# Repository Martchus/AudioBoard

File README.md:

# AudioBoard

Im Ordner Hardware befindet sich der Schaltplan als KiCAD Projekt und die Gerberdaten der Platine.

Die Software gibt es als "Basic" Version, welche die Grundlegenden Funktionen zur verfügung stellt. Auf der Basis von diesen Daten können eigene Projekte entwickelt werden.
Der Quelltext zum Matrixprojekt ist auf genau dieses Projekt zugeschnitten. Es wird dazu eine 7x6 Matrix mit WS2812 LEDs erwartete, welche alle seriell verbunden sind. Dieser Quelltext soll eher als Inspiration dienen.

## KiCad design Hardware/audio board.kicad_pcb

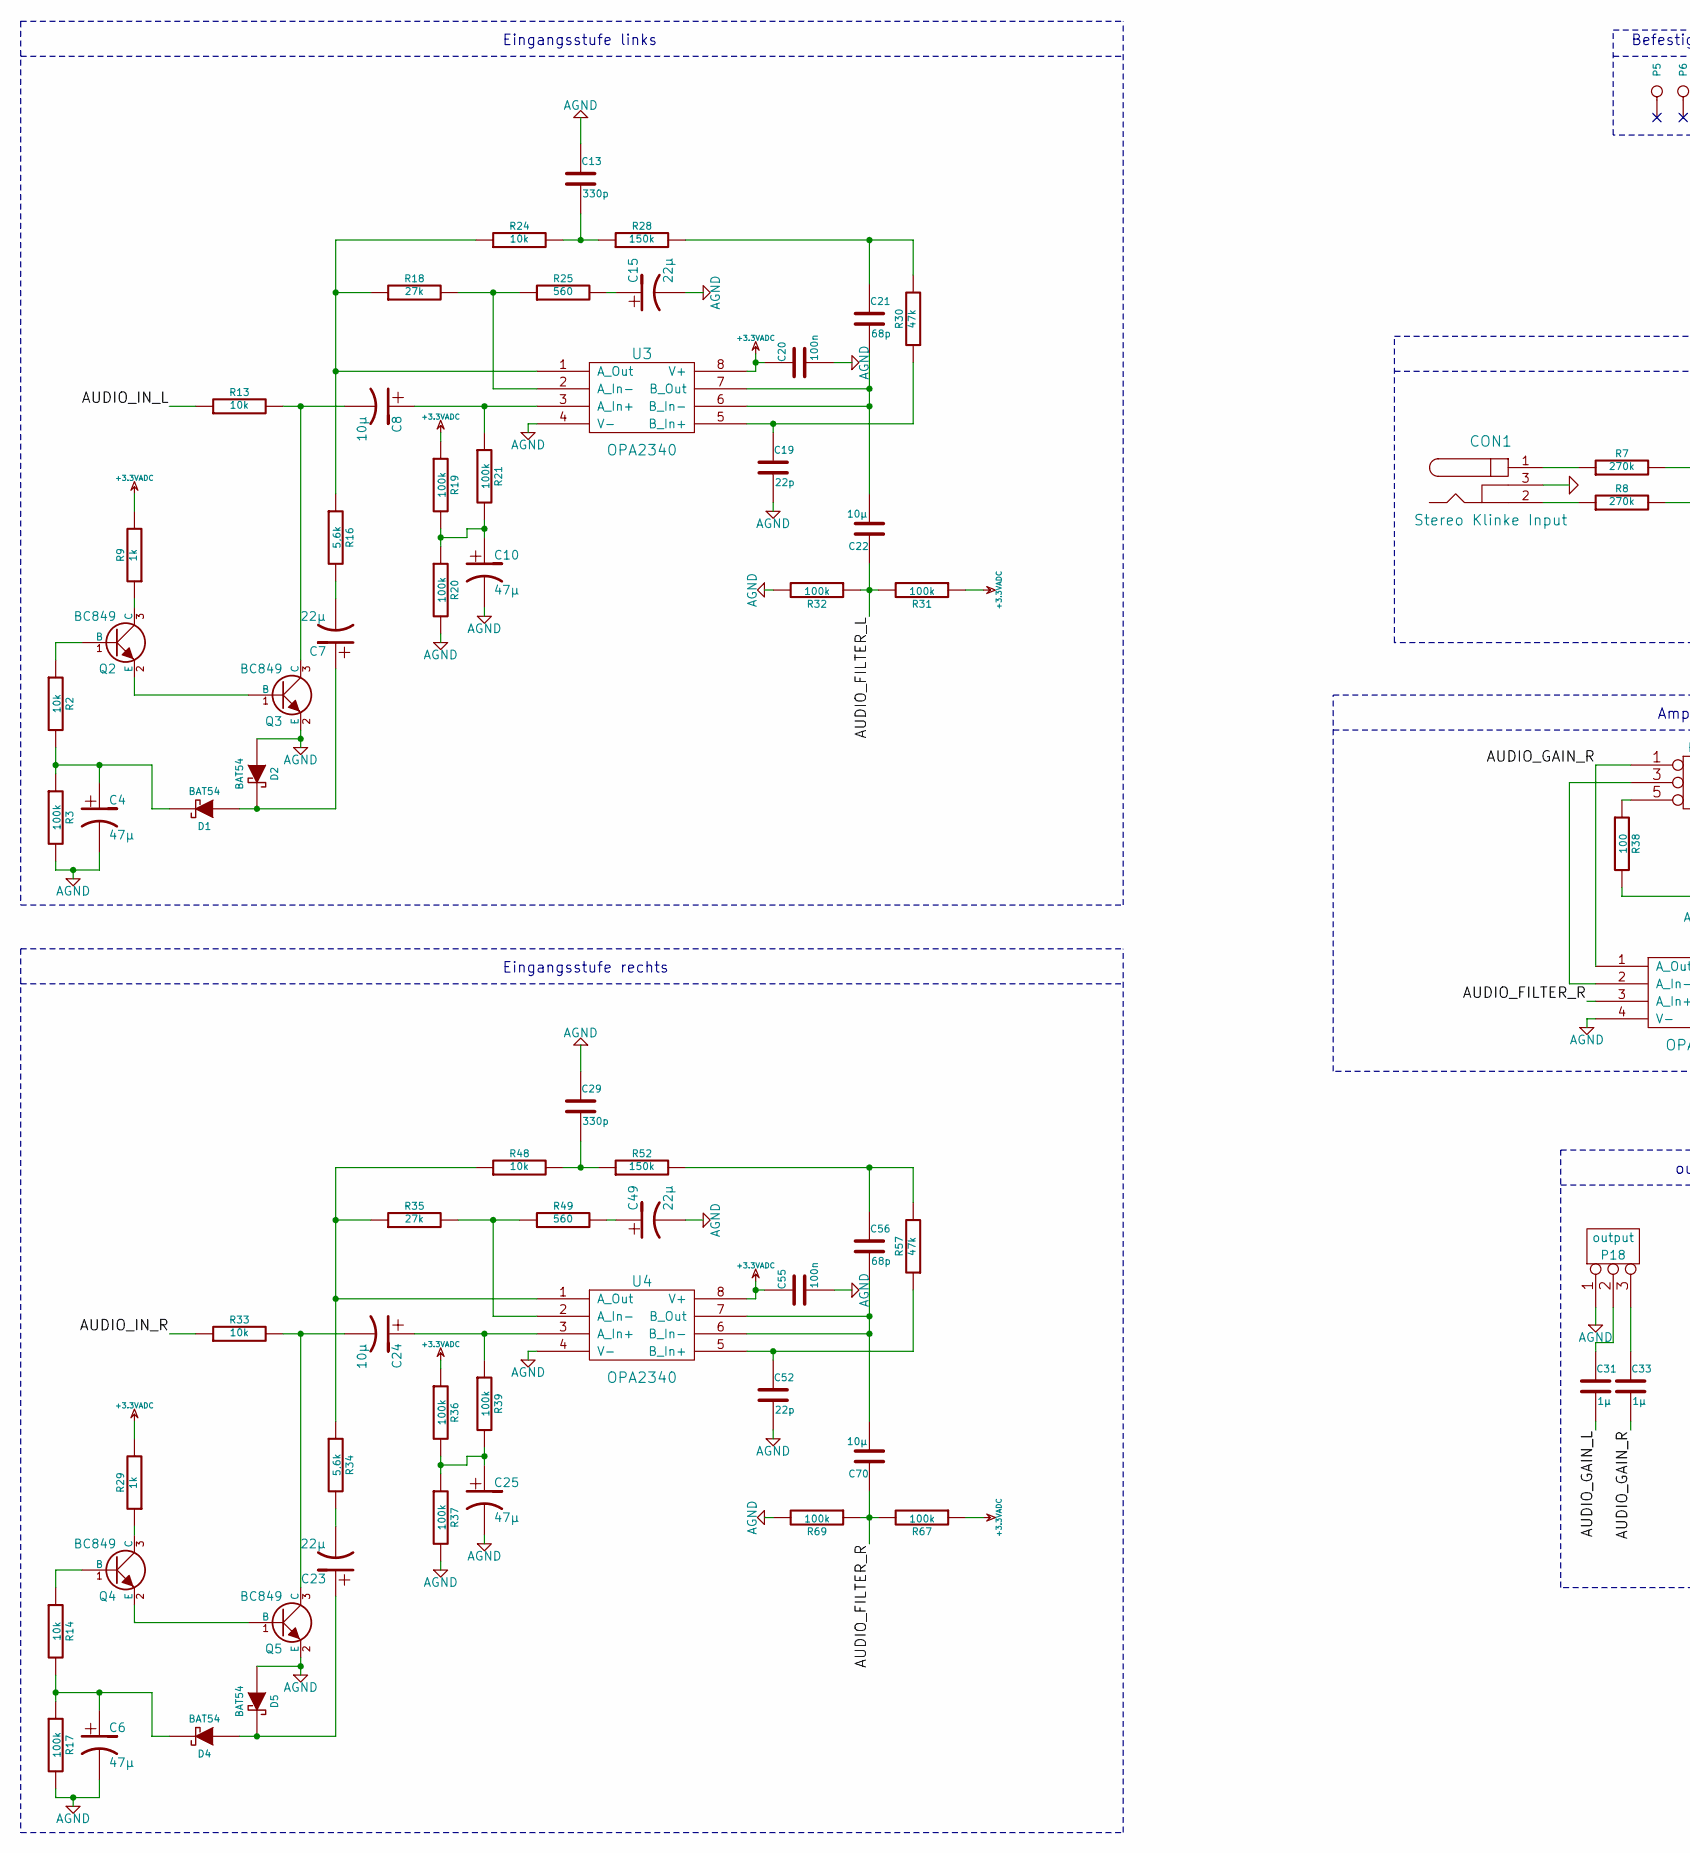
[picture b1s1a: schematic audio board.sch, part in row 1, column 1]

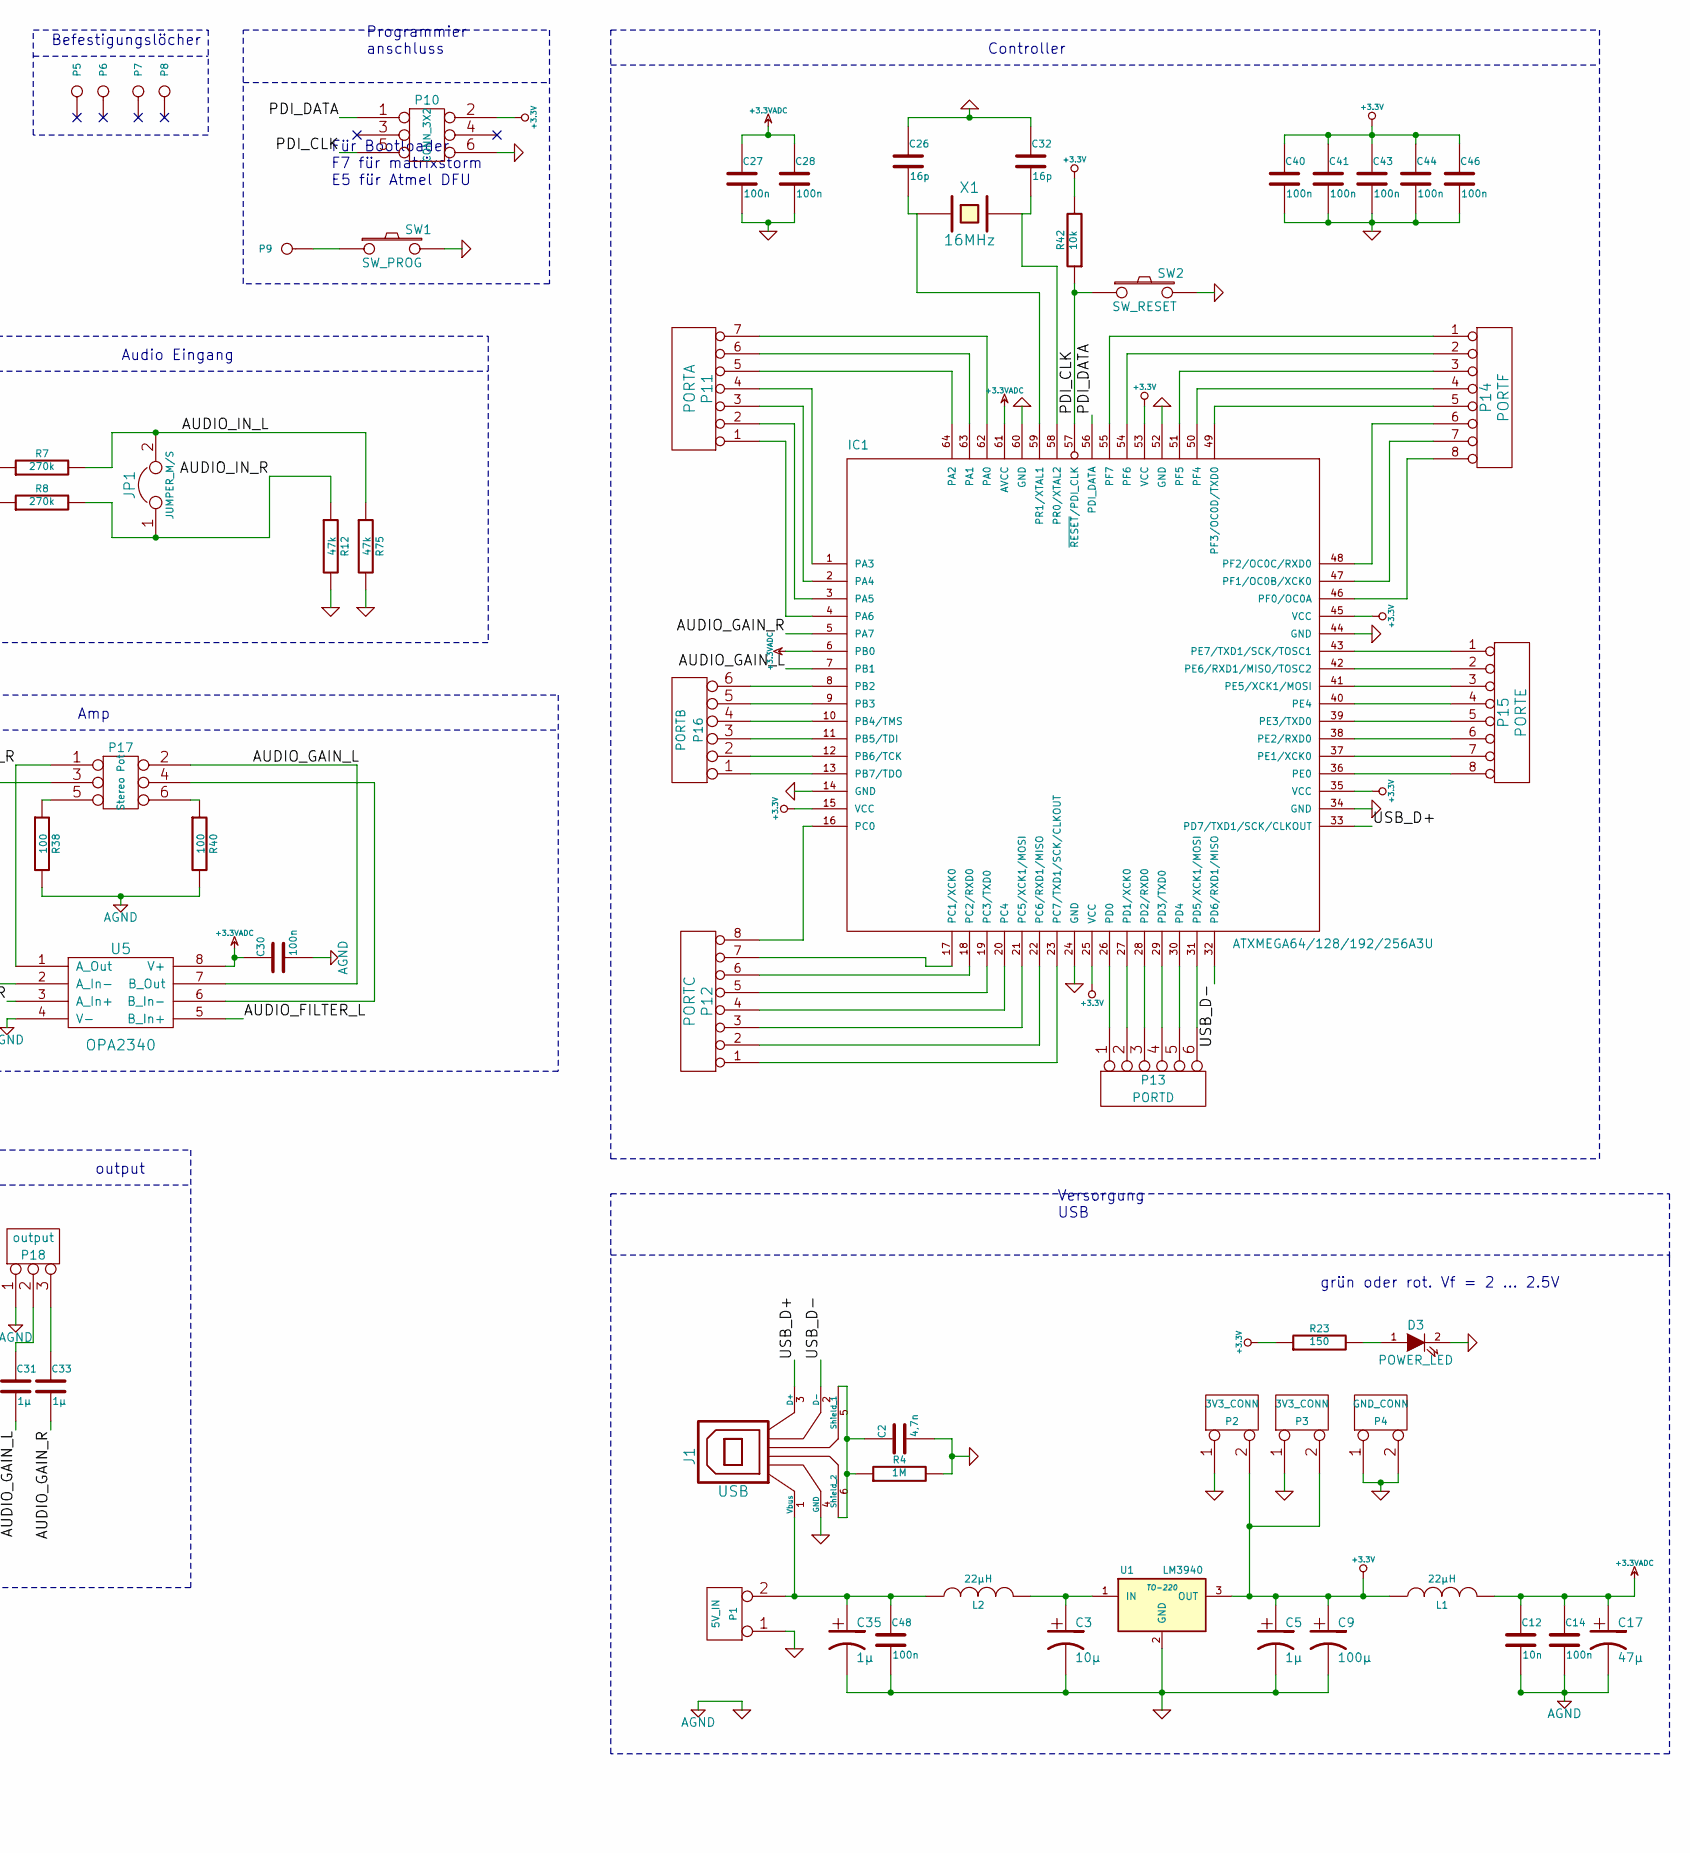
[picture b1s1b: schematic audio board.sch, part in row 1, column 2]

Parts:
C2: 4,7n
C3, C8, C22, C24, C70: 10µ
C4, C6, C10, C17, C25: 47µ
C5, C31, C33, C35: 1µ
C7, C15, C23, C49: 22µ
C9: 100µ
C12: 10n
C13, C29: 330p
C14, C20, C27, C28, C30, C40, C41, C43, C44, C46, C48, C55: 100n
C19, C52: 22p
C21, C56: 68p
C26, C32: 16p
CON1: Stereo Klinke Input
D1, D2, D4, D5: BAT54
D3: POWER_LED
IC1: ATXMEGA64/128/192/256A3U; TQFP64
J1: USB
JP1: JUMPER_M/S
L1, L2: 22µH
P1: 5V_IN
P2, P3: 3V3_CONN
P4: GND_CONN
P5, P6, P7, P8: Bohrung
P9: CONN_1
P10: CONN_3X2
P11: PORTA
P12: PORTC
P13: PORTD
P14: PORTF
P15: PORTE
P16: PORTB
P17: Stereo Pot
P18: output
Q2, Q3, Q4, Q5: BC849
R2, R13, R14, R24, R33, R42, R48: 10k
R3, R17, R19, R20, R21, R31, R32, R36, R37, R39, R67, R69: 100k
R4: 1M
R7, R8: 270k
R9, R29: 1k
R12, R30, R57, R75: 47k
R16, R34: 5,6k
R18, R35: 27k
R23: 150
R25, R49: 560
R28, R52: 150k
R38, R40: 100
SW1: SW_PROG
SW2: SW_RESET
U1: LM3940; TO-220
U3, U4, U5: OPA2340
X1: 16MHz

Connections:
+3.3V: C5.1, C9.1, C40.1, C41.1, C43.1, C44.1, C46.1, IC1.15 (VCC), IC1.25 (VCC), IC1.35 (VCC), IC1.45 (VCC), IC1.53 (VCC), L1.1, P2.2 (PM), P3.2 (PM), P10.2, R23.1, R42.2, U1.3 (OUT)
+3.3VADC: C12.1, C14.1, C17.1, C20.1, C27.1, C28.1, C30.1, C55.1, IC1.6 (PB0), IC1.61 (AVCC), L1.2, R9.2, R19.1, R29.2, R31.1, R36.1, R67.1, U3.8 (V+), U4.8 (V+), U5.8 (V+)
/AUDIO_FILTER_L: C22.1, R31.2, R32.1, U5.5 (B_In+)
/AUDIO_FILTER_R: C70.1, R67.2, R69.1, U5.3 (A_In+)
/AUDIO_GAIN_L: C31.2, IC1.7 (PB1), P17.2, U5.7 (B_Out)
/AUDIO_GAIN_R: C33.2, IC1.5 (PA7), P17.1, U5.1 (A_Out)
/AUDIO_IN_L: JP1.2, R7.2, R13.1, R75.1
/AUDIO_IN_R: JP1.1, R8.2, R12.1, R33.1
/PDI_CLK: IC1.57 (~RESET~/PDI_CLK), P10.5, R42.1, SW2.1
/PDI_DATA: IC1.56 (PDI_DATA), P10.1
/USB_D+: IC1.33 (PD7/TXD1/SCK/CLKOUT), J1.3 (D+)
/USB_D-: IC1.32 (PD6/RXD1/MISO), J1.2 (D-)
AGND: C2.2, C3.2, C4.2, C5.2, C6.2, C9.2, C10.2, C12.2, C13.1, C14.2, C15.2, C17.2, C19.2, C20.2, C25.2, C26.1, C27.2, C28.2, C29.1, C30.2, C32.1, C35.2, C40.2, C41.2, C43.2, C44.2, C46.2, C48.2, C49.2, C52.2, C55.2, CON1.3, D2.1 (A), D3.2 (K), D5.1 (A), IC1.14 (GND), IC1.24 (GND), IC1.34 (GND), IC1.44 (GND), IC1.52 (GND), IC1.60 (GND), J1.4 (GND), P1.1, P2.1, P3.1, P4.1, P4.2 (PM), P10.6, P18.1, Q3.2 (E), Q5.2 (E), R3.2, R4.2, R12.2, R17.2, R20.2, R32.2, R37.2, R38.2, R40.2, R69.2, R75.2, SW1.2, SW2.2, U1.2 (GND), U3.4 (V-), U4.4 (V-), U5.4 (V-)
unnamed: IC1.46 (PF0/OC0A), P14.8
unnamed: IC1.54 (PF6), P14.2
unnamed: IC1.51 (PF5), P14.3
unnamed: IC1.50 (PF4), P14.4
unnamed: IC1.49 (PF3/OC0D/TXD0), P14.5
unnamed: IC1.48 (PF2/OC0C/RXD0), P14.6
unnamed: IC1.47 (PF1/OC0B/XCK0), P14.7
unnamed: IC1.55 (PF7), P14.1
unnamed: P9.1, SW1.1
unnamed: IC1.43 (PE7/TXD1/SCK/TOSC1), P15.1
unnamed: IC1.42 (PE6/RXD1/MISO/TOSC2), P15.2
unnamed: IC1.40 (PE4), P15.4
unnamed: IC1.39 (PE3/TXD0), P15.5
unnamed: IC1.38 (PE2/RXD0), P15.6
unnamed: IC1.37 (PE1/XCK0), P15.7
unnamed: IC1.36 (PE0), P15.8
unnamed: IC1.64 (PA2), P11.5
unnamed: IC1.62 (PA0), P11.7
unnamed: IC1.63 (PA1), P11.6
unnamed: IC1.1 (PA3), P11.4
unnamed: IC1.2 (PA4), P11.3
unnamed: IC1.3 (PA5), P11.2
unnamed: IC1.4 (PA6), P11.1
unnamed: IC1.11 (PB5/TDI), P16.3
unnamed: C10.1, R19.2, R20.1, R21.2
unnamed: C8.2, Q3.3 (C), R13.2
unnamed: Q2.2 (E), Q3.1 (B)
unnamed: Q2.3 (C), R9.1
unnamed: C4.1, D1.3 (K), R2.2, R3.1
unnamed: Q2.1 (B), R2.1
unnamed: C7.2, R16.2
unnamed: C15.1, R25.2
unnamed: R18.2, R25.1, U3.2 (A_In-)
unnamed: C8.1, R21.1, U3.3 (A_In+)
unnamed: CON1.1, R7.1
unnamed: CON1.2, R8.1
unnamed: IC1.9 (PB3), P16.5
unnamed: IC1.8 (PB2), P16.6
unnamed: IC1.41 (PE5/XCK1/MOSI), P15.3
unnamed: IC1.12 (PB6/TCK), P16.2
unnamed: IC1.10 (PB4/TMS), P16.4
unnamed: P17.3, U5.2 (A_In-)
unnamed: C2.1, J1.5 (Shield_1), J1.6 (Shield_2), R4.1
unnamed: C3.1, L2.2, U1.1 (IN)
unnamed: D3.1 (A), R23.2
unnamed: C56.2, C70.2, U4.6 (B_In-), U4.7 (B_Out)
unnamed: IC1.16 (PC0), P12.8
unnamed: IC1.13 (PB7/TDO), P16.1
unnamed: C23.2, R34.2
unnamed: C6.1, D4.3 (K), R14.2, R17.1
unnamed: R34.1, R35.1, R48.1, U4.1 (A_Out)
unnamed: R35.2, R49.1, U4.2 (A_In-)
unnamed: C29.2, R48.2, R52.1
unnamed: C56.1, R52.2, R57.2
unnamed: C52.1, R57.1, U4.5 (B_In+)
unnamed: P17.4, U5.6 (B_In-)
unnamed: P17.6, R40.1
unnamed: P17.5, R38.1
unnamed: C31.1, P18.2 (PM)
unnamed: C33.1, P18.3
unnamed: IC1.27 (PD1/XCK0), P13.2
unnamed: IC1.20 (PC4), P12.4
unnamed: IC1.21 (PC5/XCK1/MOSI), P12.3
unnamed: IC1.22 (PC6/RXD1/MISO), P12.2
unnamed: IC1.23 (PC7/TXD1/SCK/CLKOUT), P12.1
unnamed: IC1.31 (PD5/XCK1/MOSI), P13.6
unnamed: IC1.19 (PC3/TXD0), P12.5
unnamed: IC1.26 (PD0), P13.1
unnamed: IC1.30 (PD4), P13.5
unnamed: IC1.29 (PD3/TXD0), P13.4
unnamed: IC1.28 (PD2/RXD0), P13.3
unnamed: C26.2, IC1.59 (PR1/XTAL1), X1.1
unnamed: C32.2, IC1.58 (PR0/XTAL2), X1.2
unnamed: C21.1, R28.2, R30.2
unnamed: R16.1, R18.1, R24.1, U3.1 (A_Out)
unnamed: C13.2, R24.2, R28.1
unnamed: C21.2, C22.2, U3.6 (B_In-), U3.7 (B_Out)
unnamed: C19.1, R30.1, U3.5 (B_In+)
unnamed: IC1.18 (PC2/RXD0), P12.6
unnamed: Q4.2 (E), Q5.1 (B)
unnamed: C24.1, R39.1, U4.3 (A_In+)
unnamed: C25.1, R36.2, R37.1, R39.2
unnamed: C24.2, Q5.3 (C), R33.2
unnamed: Q4.3 (C), R29.1
unnamed: Q4.1 (B), R14.1
unnamed: IC1.17 (PC1/XCK0), P12.7
unnamed: C35.1, C48.1, J1.1 (Vbus), L2.1, P1.2 (PM)
unnamed: C49.1, R49.2
unnamed: C7.1, D1.1 (A), D2.3 (K)
unnamed: C23.1, D4.1 (A), D5.3 (K)

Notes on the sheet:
Controller
Programmier anschluss
Versorgung USB
grün oder rot. Vf = 2 ... 2.5V
Für Bootloader F7 für matrixstorm E5 für Atmel DFU
Eingangsstufe links
Befestigungslöcher
Eingangsstufe rechts
Audio Eingang
Amp
output

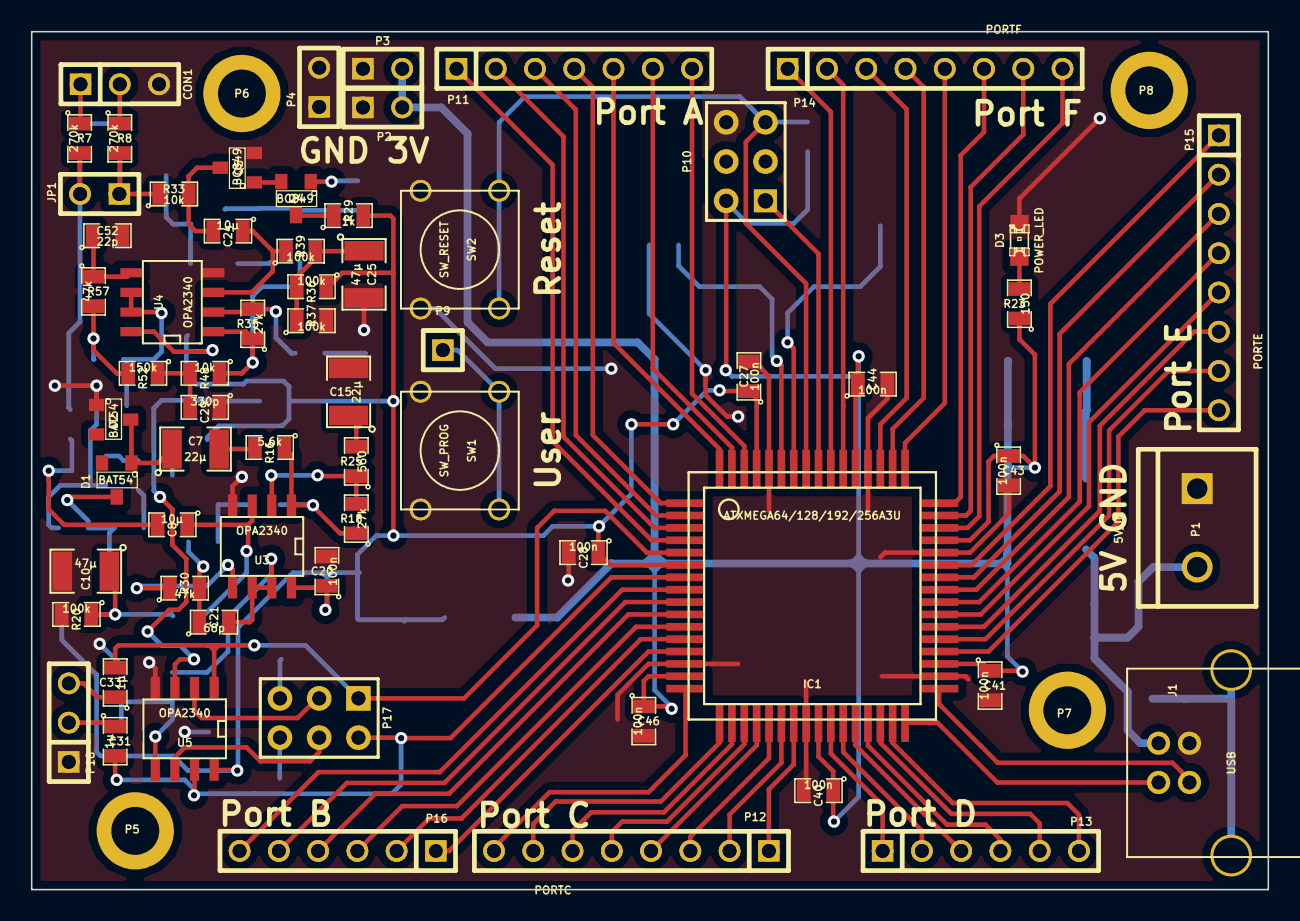
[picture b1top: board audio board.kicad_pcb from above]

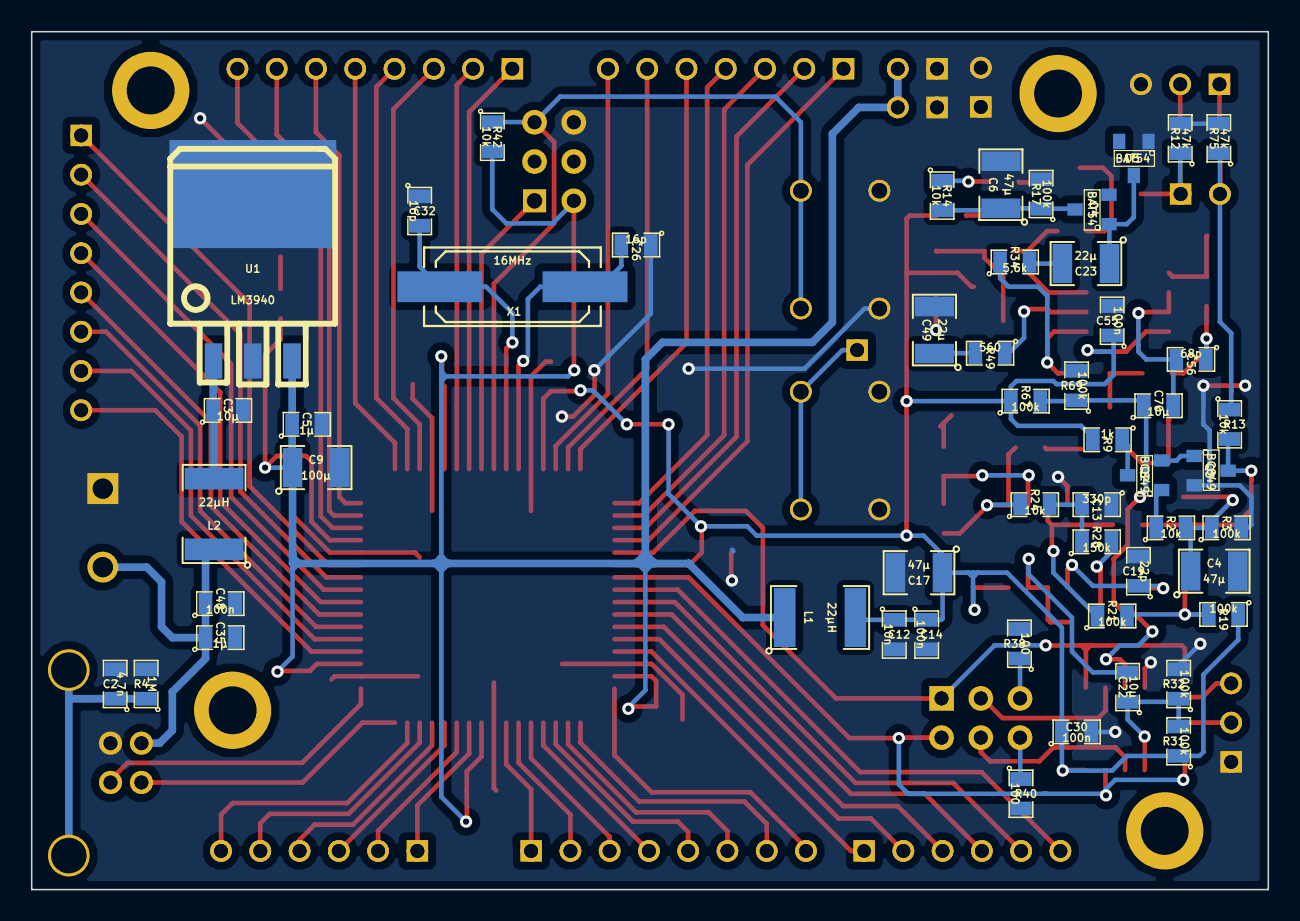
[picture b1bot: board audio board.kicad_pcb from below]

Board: 2 copper layers, 80.0 x 55.5 mm, 120 parts (52 on the bottom side), 103 nets.

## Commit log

2015-01-22 Update 1
    Hardware und Basics
2015-01-22 aufräumen
2015-01-23 basic update
2015-01-23 matrix projekt
2015-01-23 matrix
2015-02-16 update basic
